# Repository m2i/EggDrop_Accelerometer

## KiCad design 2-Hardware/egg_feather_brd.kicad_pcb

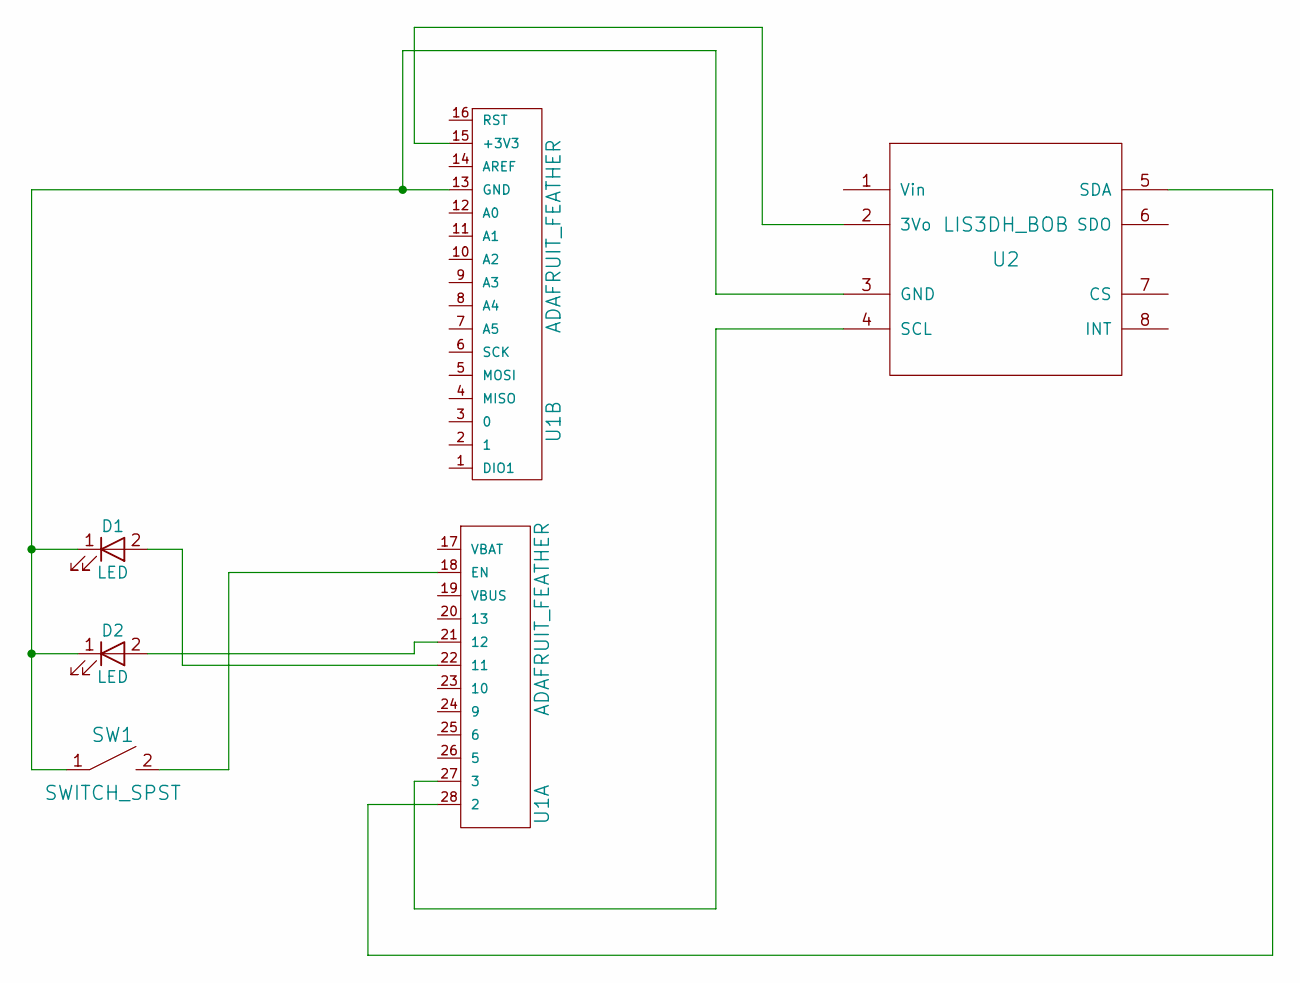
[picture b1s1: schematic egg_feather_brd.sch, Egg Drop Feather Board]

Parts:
D1, D2: LED; LED_1206
SW1: SWITCH_SPST; SW_DIP_x1_W7.62mm_Slide
U1: ADAFRUIT_FEATHER
U2: LIS3DH_BOB; Pin_Header_Straight_1x08_Pitch2.54mm

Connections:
unnamed: D1.1 (K), D2.1 (K), SW1.1, U1.13 (GND), U2.3 (GND)
unnamed: D1.2 (A), U1.22 (11)
unnamed: D2.2 (A), U1.21 (12)
unnamed: SW1.2, U1.18 (EN)
unnamed: U1.15 (+3V3), U2.2 (3Vo)
unnamed: U1.27 (3), U2.4 (SCL)
unnamed: U1.28 (2), U2.5 (SDA)

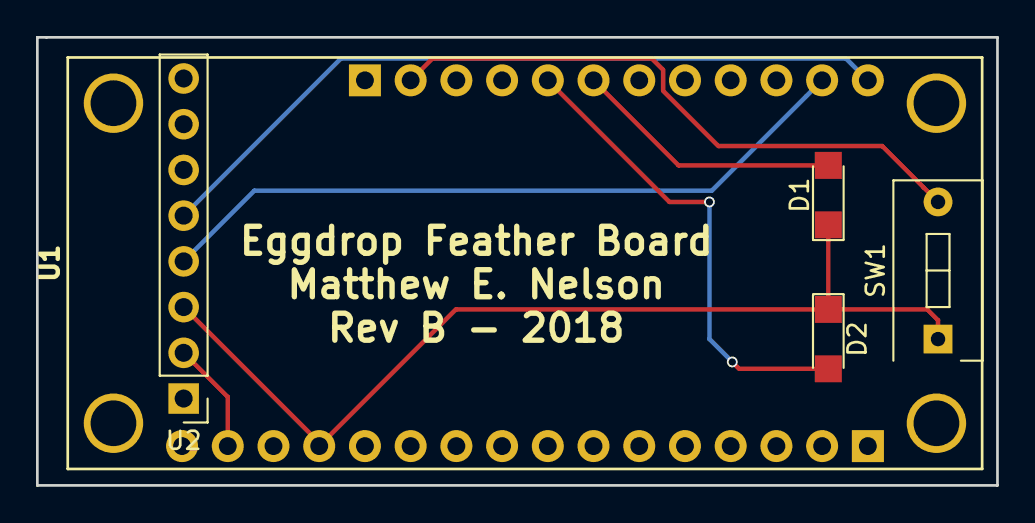
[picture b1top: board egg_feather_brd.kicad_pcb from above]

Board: 2 copper layers, 53.3 x 24.9 mm, 5 parts (0 on the bottom side), 7 nets.

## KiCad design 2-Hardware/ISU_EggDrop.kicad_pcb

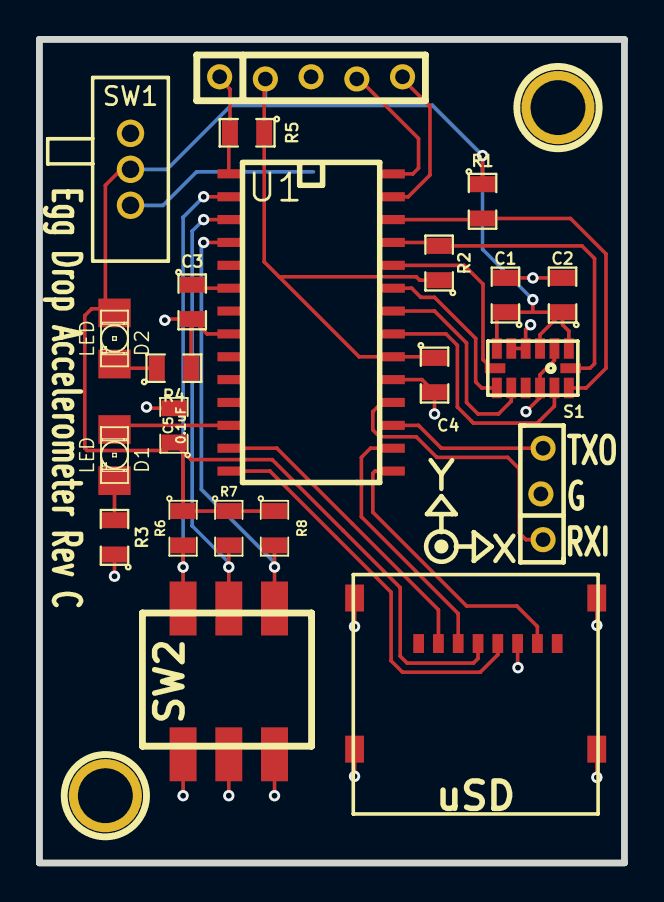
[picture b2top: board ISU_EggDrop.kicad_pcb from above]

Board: 2 copper layers, 32.5 x 45.7 mm, 26 parts (1 on the bottom side), 25 nets.

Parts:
1PIN, 1PIN#2: P***; 1pin
AXIS_Z-UP: Val**; AXIS_Z-UP
BT1: CR2032; BATT_CR2032_MPD
C1: 1 uF; SM0805
C2, C4: 0.1 uF; SM0805
C3: 10 uF; SM0805
C5: 0.1uF; SM0805
D1, D2: LED; LED-1206
K1: CONN_3; CONN_1x3
P1: CONN_5; CONN_1x5
R1, R2: 4.7K; SM0805
R3, R4: 330; SM0805
R5: 10K; SM0805
R6, R7, R8: 10k; SM0805
S1: ADXL345; LGA-14
SW1: SWITCH_SPDT; SWITCH_DPST_TE
SW2: SWITCH_DIP_3
U1: PIC18F27J13; SO28
uSD: uSD; MICRO_SD_HINGE_AMP

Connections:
+3.3V: C1.1, C2.1, C4.1, C5.1, D2.1, P1.2, R1.1, R2.1, R5.1, R6.1, R7.1, R8.1, S1.1, S1.3, S1.6, SW1.2, U1.20, uSD.4
/ALT: S1.7, U1.24
/CS: U1.13, uSD.2
/INT1: S1.8, U1.23
/INT2: S1.9, U1.22
/MCLR: P1.1, R5.2, U1.1
/MISO: U1.15, uSD.7
/MOSI: U1.16, uSD.3
/PGC: P1.5, U1.27
/PGD: P1.4, U1.28
/RANGE_0: R6.2, SW2.1, U1.2
/RANGE_1: R7.2, SW2.2, U1.3
/RX: K1.1, U1.18
/SCL: R2.2, S1.14, U1.25
/SCk: U1.14, uSD.5
/SDA: R1.2, S1.13, U1.26
/SDO: S1.12, U1.21
/TEST: R8.2, SW2.3, U1.4
/TX: K1.3, U1.17
GND: BT1.2, C1.2, C2.2, C3.2, C4.2, C5.2, K1.2, P1.3, R3.1, R4.2, S1.2, S1.4, S1.5, S1.11, SW2.4, SW2.5, SW2.6, U1.8, U1.19, uSD.6, uSD.SHLD
unnamed: D2.2, R4.1
unnamed: D1.2, R3.2
unnamed: BT1.1, SW1.1
unnamed: C3.1, U1.6
unnamed: D1.1, U1.12

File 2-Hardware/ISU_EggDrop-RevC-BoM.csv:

CR2032,1,"BT1",BC2032-F1-ND,Memory Protection Devices,BC2032-F1
0.1uF,3,"C2 C4 C5",311-1141-1-ND,Yageo,CC0805KRX7R8BB104
1uF,1,"C1",478-3050-1-ND,AVX Corporation,TAJR105M016RNJ
10uF,1,"C3",490-1746-1-ND,Murata Electronics,GRM21BF50J106ZE01L
uSD,1,"CARD1",101-00303-68-1-ND,Amphenol Commercial Products,101-00303-68
LED,2,"D1 D2",754-1141-1-ND,Kingbright Company,APT3216SGC
CONN_3,1,"K1"
CONN_5,1,"P1"
330,2,"R3 R4",P330CCT-ND,Panasonic Electronic Components,ERJ-6ENF3300V
4.7K,2,"R1 R2",P4.70KCCT-ND,Panasonic Electronic Components,ERJ-6ENF4701V
10k,4,"R5 R6 R7 R8",P10.0KCCT-ND,Panasonic Electronic Components,ERJ-6ENF1002V
ADXL345,1,"S1",ADXL345BCCZ-RLCT-ND,Analog Devices,ADXL345BCCZ-RL
SWITCH_SPDT,1,"SW1",450-1635-ND,TE Connectivity,SSJ12R04
~,1,"SW2",CKN6060-ND,C&K Components,SDA03H0SBD
PIC18F27J13,1,"U1",PIC18F27J13-I/SO-ND,Microchip Technology,PIC18F27J13-I/SO

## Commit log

2013-09-21 Added part datasheets to the repository.
2013-09-21 Added the hardware layout files for the EggDrop board.
2013-09-21 MATLAB script to parse logged data from the accelerometer.
2014-08-10 Firmware for rev C.
2014-09-03 Added enclosure files
2014-09-05 Update to enclosure
    Minor changes based on prototype egg printed
2014-09-07 Update
    Update to T-lock based on recent 3D print test.
2015-06-11 Update
    Update to new part for 3D printed egg
2015-06-15 Final edit
    Final edit to new enclosure for a test print.
2015-08-06 First revision of the Light Blue Bean firmware
    Mostly functional version, needs testing.
2015-08-06 Minor change to 3D enclosure
2015-08-06 Added light pipe
    Added cutout for light pipe
2015-08-07 Minor adjustments
    Minor update to placement of the light pipe, changed thickness on
    T-lock for more secure lock. Deleted old STL.
2015-08-07 Update
    The actual update to the file.
2015-08-11 test code
    Test code for restructuring the code
2015-08-11 additional testing, debugging
    not ready yet
2015-08-31 Update to FW
2016-08-14 New branch
    New branch, cleaned out old code, started new code based on new
    hardware.
2016-08-28 First version
    First compilable version with sensor read and wrting to the SD Card
2016-08-28 Revision 1 code
    Working code, compiles and runs as expected on Feather board.
2016-08-28 Updated eclosure
    Updated enclosure to match new hardware. Had to get rid of the T-locks,
    not enough room.
2016-09-01 Fixed errors
    Fixed calculation error in magnitude. Decreased sensitivity for
    triggering broken egg.
2017-06-30 New featherboard shield
2017-07-07 Changed to BOB circuit
2017-07-09 Revamp on enclosure, added first run PCB board
    Revamped the enclosure for test print. Added PCB based on circuit for
    first run boards for testing.
2017-07-10 Moved part off pin 13 to pin 11
    Moved part off pin 13, new part placement on board
2017-07-11 Final revisions to board, routed
    Final design for first run. Board routed and sent to manufacturing.
2017-07-11 update to enclosure
    Added mounting holes, ready for test print
2017-08-26 Updates to egg
2017-08-26 fix to battery voltage reading
2017-08-26 Minor update
2017-08-28 Eggbreak adjustment
    adjustment for when a break is detected.
2018-02-19 Changed LEDs
    Changed to surface mount LEDs
2018-02-19 Schematic update
2018-07-25 Updates for KiCad 5, routed board for test run
2018-08-20 Fixed running average
    Uses span of 5
2018-08-20 fixed running average
    Wrong value was used for span size
2018-08-23 Fixes to variables
    Fixed an error with int to float. Adjusted break point.
2018-08-23 Updated SD header
2018-08-26 update to gitignore
